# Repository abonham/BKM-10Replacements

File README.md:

# BKM-10Replacements
BKM-10Replacements are cheap microcontroller based alternative for the Sony BKM-10R control unit typically used with Sony broadcast monitors like the BVM-D20F1a/e/u.

The most up-to-date version is BKM10-Rp2040, based on the Raspberry Pico. See the docs in that directory for setup instructions.

## Why?
BVM and PVM CRTs are rather popular with retro gaming enthusiasts, but they are being priced out of reach for the average fan. I managed to rescue a BVM-D20F1A that was destined for e-waste. Of course it was missing the control unit and it was stuck on the SDI input. One spare Arduino Nano, a couple of components, and a lot of swearing later, I had something good enough to use the menus to change inputs and do basic setup. With the help of Martin (@skumlos), this evolved in to a universal IR based replacement.

## What's it do?
Allows the use of almost any IR remote you might have lying around to control any BVM compatible with the BKM-10R. It's configurable through a learning mode, so it's kind of like using a universal remote control, if you remember those from the late 90s. All the buttons on the BKM-10R are replicated, and all status LEDs are displayed on an OLED screen.

There's no problem assembling this on a breadboard, but there are KiCAD schematics, PCB designs and gerber files included if you'd like a more polished finised product.

## Warning
I'm not an electrical engineer. I don't know enough to know when I'm doing something stupid or dangerous. Goes without saying that there is absolutely no warranty; if your precious monitor explodes, I will be very sympathetic and sorry, but that's all. Proceed at your own risk.

If you want to build the PCB version, there are some SMT components, so a least a bit of soldering experience is highly recommended.
## Thanks
I found the control codes on an anonymous [pastebin](https://pastebin.com/aTUWf33J), so must thank this unknown hero.

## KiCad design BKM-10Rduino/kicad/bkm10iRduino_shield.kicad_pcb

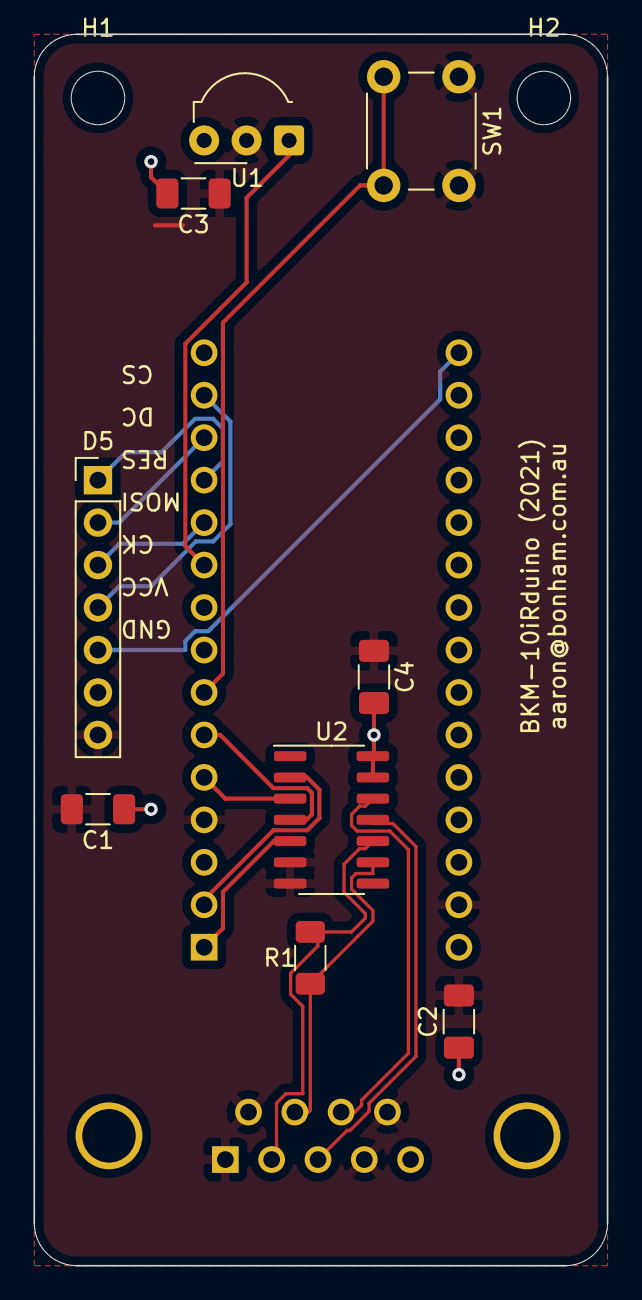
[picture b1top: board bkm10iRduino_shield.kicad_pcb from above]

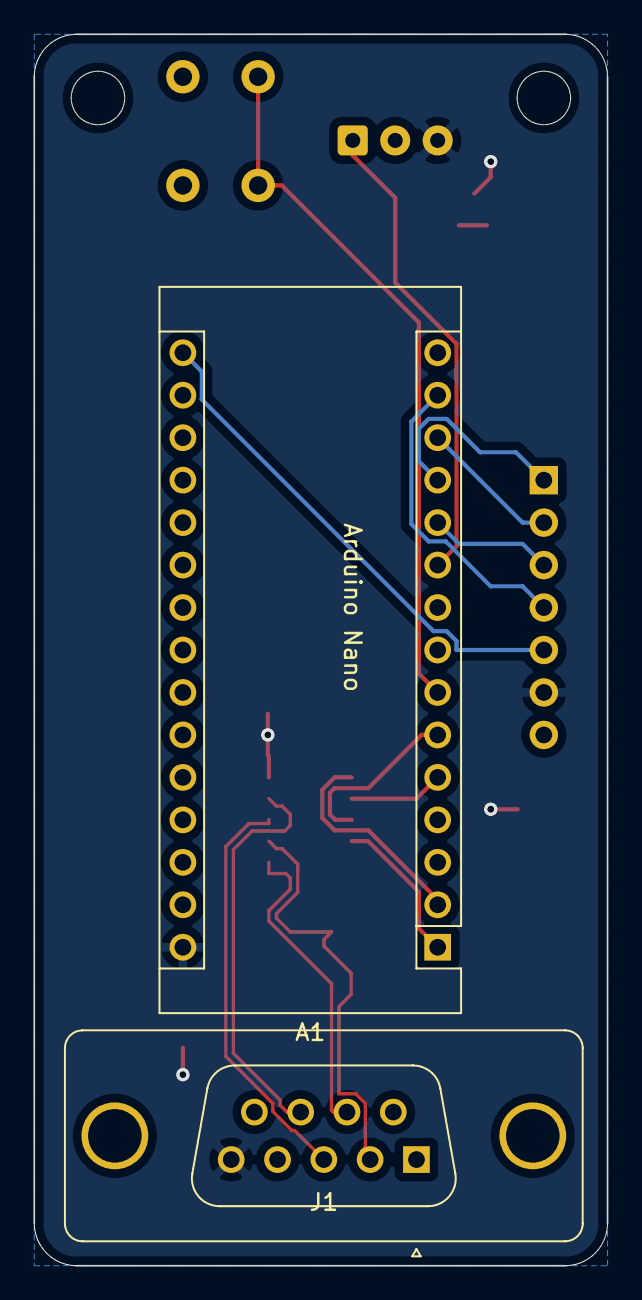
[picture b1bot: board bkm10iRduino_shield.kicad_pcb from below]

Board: 2 copper layers, 34.3 x 73.7 mm, 13 parts (2 on the bottom side), 17 nets.

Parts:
A1: Arduino_Nano_Every; Arduino_Nano
C1, C2, C3, C4: C_Small; C_1206_3216Metric_Pad1.33x1.80mm_HandSolder
D5: SH1106; PinHeader_1x07_P2.54mm_Vertical
H1, H2: MountingHole; MountingHole_3.2mm_M3
J1: DB9_Male; DSUB-9_Male_Vertical_P2.77x2.84mm_MountingHoles
R1: R; R_1206_3216Metric_Pad1.30x1.75mm_HandSolder
SW1: SW_SPST; SW_PUSH_6mm_H5mm
U1: TSOP343xx; Vishay_MOLD-3Pin
U2: ADM3063EARZ-ND; SOIC-14_3.9x8.7mm_P1.27mm

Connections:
AB+: J1.3, U2.11
AB-: J1.8, U2.12
CS: A1.12, D5.1
DC: A1.13, D5.2
GND: A1.4, A1.29, C1.2, C2.2, C3.1, C4.1, D5.7, J1.1, J1.4, J1.6, J1.9, SW1.1, U1.2, U2.6, U2.7
IR_OUT: A1.10, U1.1
LEARN_BUTTON_IN: A1.7, SW1.2
MOSI: A1.14, D5.4
RES: A1.11, D5.3
RS485_RX: A1.2, U2.2
RS485_RX_ENABLE: A1.5, U2.3
RS485_TX: A1.1, U2.5
RS485_TX_ENABLE: A1.6, U2.4
SCK: A1.16, D5.5
VCC: A1.30, C1.1, C2.1, C3.2, C4.2, D5.6, J1.5, U1.3, U2.13, U2.14
YZ+: J1.7, R1.1, U2.9
YZ-: J1.2, R1.2, U2.10

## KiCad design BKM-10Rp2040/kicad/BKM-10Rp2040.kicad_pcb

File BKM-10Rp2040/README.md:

Board | DB9
__
1 | 1
2 | 8
3 | 7
5 | 5
7 | 3
8 | 2

/*** Thank you to the anonymous pastebin hero responsible for providing the control codes ***/

  https://pastebin.com/aTUWf33J
  BKM-10R Protocol
  Version 1 - May 16, 2016
  License: CC0

  The BKM-10R is a remote control used for Sony BVM CRT televisions. It is
  required to control some CRTs without built in control, such as the BVM-20F1U.

  The protocol is vaguely similar to the one used to control Sony VCRs:
  ftp://ftp.sgi.com/sgi/video/rld/vidpage/s9pin.html

  This document currently only applies to the CONTROL connection, not to the
  REMOTE 1 input/output, though it's expected that they are similar.

  == Pinout ==

  The remote control and CRT are connected with straight through male-male DE9
  cable.

  Female DB-9, BKM-10R side:
  1. GND
  2. /TXD
  3. RXD
  4. GND
  5. +5V
  6. GND
  7. TXD
  8. /RXD
  9. GND

  Since a straight through cable is used, TXD on the remote side is RXD on the
  CRT side. +5V is supplied from the CRT to power the remote.

  == Protocol ==

  Full duplex RS-422, 38400 baud, 8N1 (the Sony VCR protocol uses odd parity, but
  that seems not to be the case here). If you only want to control the CRT,
  half duplex RS-485 is electrically compatible.

  == Bank ==

  There are multiple "banks" that can be switched via 3 byte commands:
  0x49 0x45 0x4E - "IEN" - encoders
  0x49 0x53 0x57 - "ISW" - switches
  0x49 0x4C 0x45 - "ILE" - leds
  0x49 0x43 0x43 - "ICC" - ??
  0x49 0x4d 0x54 - "IMT" - ??

  The remote lazily switches banks when needed.

  == Keypresses ==

  Each keydown sends 0x44, then group, then mask.
  0x44 <group> <mask>

  The SHIFT key is "just another key" - state is kept on the CRT. Shifted labels
  are listed after non-shifted labels.

  You must be in the "ISW" bank first.

  <group> <mask> - label
  0x03 0x01 - SHIFT
  0x03 0x02 - OVERSCAN / 16:9
  0x03 0x04 - HORIZ SYNC VIEW / SYNC
  0x03 0x08 - VERT SYNC VIEW / BLUE ONLY
  0x03 0x10 - MONO / R
  0x04 0x01 - APT / G
  0x04 0x02 - COMB / B
  0x04 0x04 - F1 / F3
  0x04 0x08 - F2 / F4
  0x04 0x10 - SAFE AREA / ADDRESS
  0x02 0x40 - UP
  0x02 0x80 - DOWN
  0x02 0x10 - MENU
  0x02 0x20 - ENTER
  0x02 0x08 - PHASE MANUAL
  0x02 0x04 - CHROMA MANUAL
  0x02 0x02 - BRIGHT MANUAL
  0x02 0x01 - CONTRAST MANUAL
  0x00 0x01 - 0
  0x00 0x02 - 1
  0x00 0x04 - 2
  0x00 0x08 - 3
  0x00 0x10 - 4
  0x00 0x20 - 5
  0x00 0x40 - 6
  0x00 0x80 - 7
  0x01 0x01 - 8
  0x01 0x02 - 9
  0x01 0x04 - Del
  0x01 0x08 - Ent
  0x01 0x10 - POWER (but see below)
  0x01 0x20 - DEGAUSS

  == POWER ==

  You only need to send a POWER keypress to turn on the monitor, but for some
  reason the remote does more.

  Power sends five 3-byte sequences:
  0x49 0x53 0x57 - switch bank
  0x44 0x01 0x10 - POWER switch
  (1s pause)
  0x49 0x43 0x43 - CC bank?
  0x49 0x4d 0x54 - MT bank?
  0x44 0x33 0x31 - switch?

  CRT responds with:
  0x49 0x43 0x43 - CC bank?
  <full led state report>
  0x49 0x4d 0x54 - MT bank?
  <full led state report>

  == Encoders ==

  Dials are rotary encoders that send 3 bytes:
  0x44 <encoder id id> <ticks>

  Ticks is a two's complement byte indicating how far the dial has turned since
  the last message. The remote sends messages about every 100ms when the dial
  is turning.

  You must be in the "IEN" bank first.

  0x03 - PHASE
  0x02 - CHROMA
  0x01 - BRIGHT
  0x00 - CONTRAST

  == LEDs ==

  LEDs use the same groups and masks as keypresses. Every time the CRT needs to
  change the lights, it changes to the LED bank:

  0x49 0x4c 0x45

  then sends changed switch groups:

  0x44 <group> <mask>

  where <mask> is all of the active LED masks OR'd together.

  == Memory Card ==

  Nobody cares.

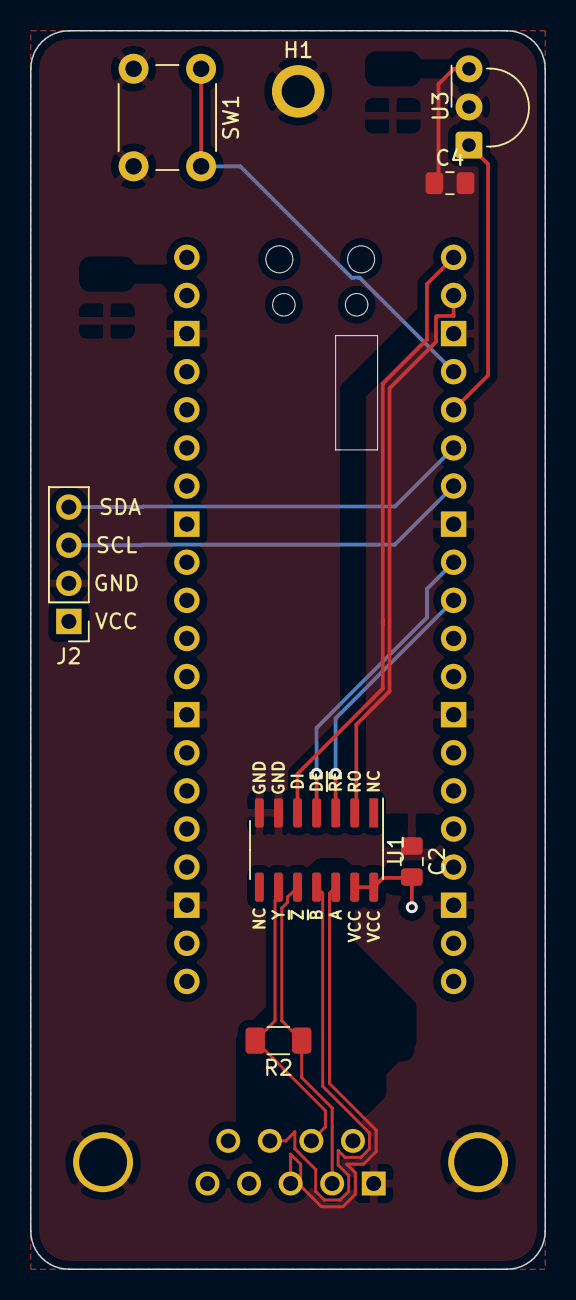
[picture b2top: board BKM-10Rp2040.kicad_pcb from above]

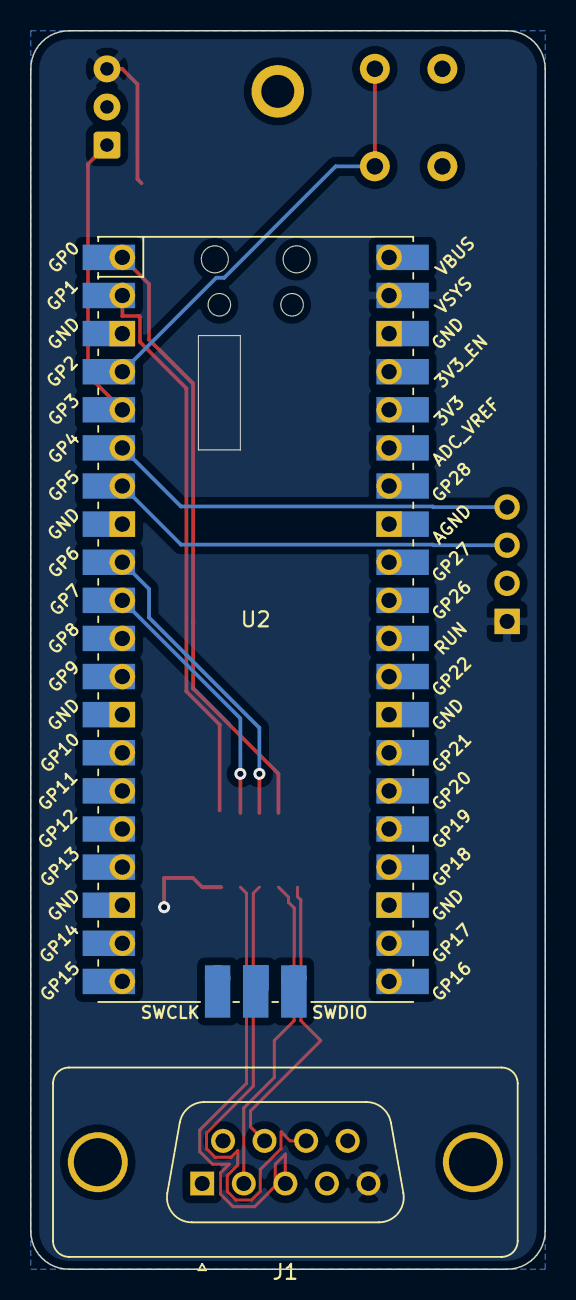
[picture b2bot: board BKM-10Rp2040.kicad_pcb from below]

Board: 2 copper layers, 34.3 x 82.5 mm, 10 parts (2 on the bottom side), 14 nets.

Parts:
C2, C4: 0.1uF; C_0805_2012Metric_Pad1.18x1.45mm_HandSolder
H1: MountingHole_Pad; MountingHole_2.2mm_M2_ISO7380_Pad
J1: DB9_Female_MountingHoles; DSUB-9_Female_Vertical_P2.77x2.84mm_MountingHoles
J2: Conn_01x04; PinHeader_1x04_P2.54mm_Vertical
R2: 60R; R_1206_3216Metric_Pad1.30x1.75mm_HandSolder
SW1: SW_DPST_x2; SW_PUSH_6mm
U1: ADM3063EARZ-ND; SOIC-14_3.9x8.7mm_P1.27mm
U2: Pico; RPi_Pico_SMD_TH
U3: TSOP335xx; Vishay_MINIMOLD-3Pin

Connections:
+5V: C2.2, C4.1, J1.5, J2.1, U1.13, U1.14, U2.39, U3.3
DE: U1.4, U2.9
GND: C2.1, C4.2, H1.1, J1.0, J1.1, J2.2, SW1.2, U1.6, U1.7, U2.3, U2.8, U2.13, U2.18, U2.23, U2.28, U2.38, U3.2
IR: U2.5, U3.1
LEARN: SW1.1, U2.4
RX: U1.2, U2.2
RXD+: J1.3, U1.12
RXD-: J1.8, U1.11
SCL: J2.3, U2.7
SDA: J2.4, U2.6
TX: U1.5, U2.1
TXD+: J1.7, R2.2, U1.9
TXD-: J1.2, R2.1, U1.10
~RE~: U1.3, U2.10

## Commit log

2022-01-26 initial migration
2022-03-05 trying to get display working on SH1106 displays
2022-03-05 fix upload port
2022-03-06 fix display on SH1106
2022-03-06 cad files for case
2022-03-13 add new case models
2022-03-31 start adding button support back in
2022-03-31 super quick buton support
2022-04-03 add compiled UF2
2022-04-05 add updated uf2 for different displays
2022-04-10 start on documentation
2022-04-10 see if we can get github actions working
2022-04-10 fix action
2022-04-11 pin lib version
2022-04-11 matrix github action
2022-04-11 matrix
2022-04-11 fix matrix
2022-04-11 only one os
2022-04-11 better matrix?
2022-04-11 again
2022-04-11 once more
2022-04-11 try archive?
2022-04-11 add archive dir
2022-04-11 no fast fail
2022-04-11 typo
2022-04-11 archive name
2022-04-11 move docs to correct place
2022-04-11 update docs
2022-05-01 fix remote learning and add new defult IR remote
2022-05-04 change defualt remote, refactor
2022-05-09 minor refactor
2022-09-01 add firmware files
2022-09-04 add degauss on quick press
